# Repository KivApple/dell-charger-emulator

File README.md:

# dell-charger-emulator
Emulator of original Dell charger using ATTINY85

Power adapter for Dell laptops contains IC to determine adapter capabilities (watts, voltage, current).
If you connect an unoriginal adapter, the laptop refuses to charge the battery.
This project allows to use the cheap and small microcontroller ATTINY85 for emulating the answers
of the original adapter to the requests of the laptop.

You can configure adapter settings in the file eeprom-data.hex. This file contains EEPROM data in Intel Hex format.
Format of Dell charger identification shown below:

| Offset | Length | Content                 | Description              |
|--------|--------|-------------------------|--------------------------|
|      0 |      4 | DELL                    | Manufacturer identifier  |
|      4 |      4 | 00AC                    | Adapter type             |
|      8 |      3 | 045                     | Watts (45W)              |
|     11 |      3 | 195                     | Tenths of a volt (19.5V) |
|     14 |      3 | 023                     | Tenths of amps (2.3A)    |
|     17 |     23 | CN0CDF577243865Q27F2A05 | Serial number            |
|     40 |      2 | 0x3D 0x94               | CRC-16/ARC (LSB first)   |

The description may not be entirely accurate. I'll be glad if you clarify.

You can use Python utility dell-charger-data-editor.py to easily change this values.

You must flash the EEPROM data together with the program code. Later you can only re-write EEPROM.

**Warning: do not mask the weak power adapter to a more powerful one. This can lead to hardware damage.**

You need ATTINY25, ATTINY45 or ATTINY85 MCU (you may need to change compiler flags in Makefile) running at 8 MHz (the internal RC-oscillator is suitable, but if desired, you can use an external crystal - adjust the fuses accordingly). The Dell power adapter connector has three pins - GND, VOUT (19V) and ID. Connect the ID to the PB2 pin of the microcontroller. Also provide 3.3V power for MCU (you can use a simple linear regulator 78L33 to make the desired voltage from 19V).

## Reading and writing EEPROM

You can read and write EEPROM using dell-charger-data-editor.py (see console menu of this utility).

You need connect OneWire bus to any USB-UART adapter using simple schematic with diode:

                        VCC 
                        _|_
                       |  | 4.7kOhm for 9600 baud
                       |__|
                        |
TXD --------|<|----*----*--- ID
                   |
RXD ----------------

GND ------------------------ GND

**Warning: USB-UART adapter should use 3.3V or 5V logic levels. 12V levels will damage EEPROM IC.**

You can read by this utility both original EEPROM and emulated by AVR. You can write only emulated EEPROM.

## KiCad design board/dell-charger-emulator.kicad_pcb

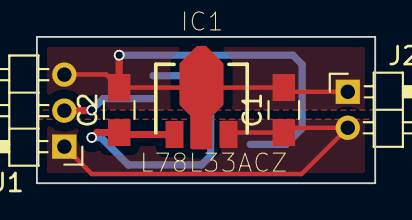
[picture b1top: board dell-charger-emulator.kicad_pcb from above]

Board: 2 copper layers, 18.8 x 8.1 mm, 6 parts (1 on the bottom side), 4 nets.

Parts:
C1: 330n; C_0805_HandSoldering
C2: 100n; C_0805_HandSoldering
IC1: L78L33ACZ; SOT-89-3
J1: CONN_01X03; Pin_Header_Angled_1x03_Pitch2.00mm
J2: CONN_01X02; Pin_Header_Angled_1x02_Pitch2.00mm
U1: ATTINY85-20SU; SOIC-8_3.9x4.9mm_Pitch1.27mm

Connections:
+3V3: C2.1, IC1.1, U1.8
GND: C1.2, C2.2, IC1.2, J1.3, J2.1, U1.4
unnamed: J1.2, U1.7
VCC: C1.1, IC1.3, J1.1, J2.2

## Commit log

2017-09-10 Moved data to ROM
2017-09-10 Move address to PROGMEM Small fix
2017-09-10 Bugfixes and optimizations
2017-09-10 Disable USI for reduce current
2017-09-10 Switch all pins to input pullup state on startu[ Fuses
2017-09-11 Some improvements
2017-09-11 First really working version
2017-09-11 Added schematic and PCB layout
2017-09-13 Update board
2017-09-13 Move charger data to EEPROM Added Python utility to edit EEPROM
2017-09-13 Enable to update EEPROM by 1wire
2017-09-13 Added EEPROM read and write functional to Python utility
2017-09-13 Small fix
